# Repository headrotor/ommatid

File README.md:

# ommatid

Code and design files for my Ommatid spherical display/sensor array. 

* Here's an [Instructable about the enclosure and dome fabrication](http://www.instructables.com/id/Ommatid-Spherical-Display-constructing-the-enclosu/)
* Here's an [Instructable about the electronics and software](http://www.instructables.com/id/Ommatid-Spherical-Display-Electronics-Programming-/)

Here are the construction and code files:

* `cad` -- 3D cad files. Likely not so useful unless you have access to a Stratasys Objet 
* `PCB` -- Schematic and printed circuit board design files
* `firmware` -- C code for ATTiny firmware for PCBs
* `code` -- host code (Python) for Ommatid.
* `sim` -- simulator, in [processing.org](http://processing.org) Python environment

NB: code is still very much a work in progress!

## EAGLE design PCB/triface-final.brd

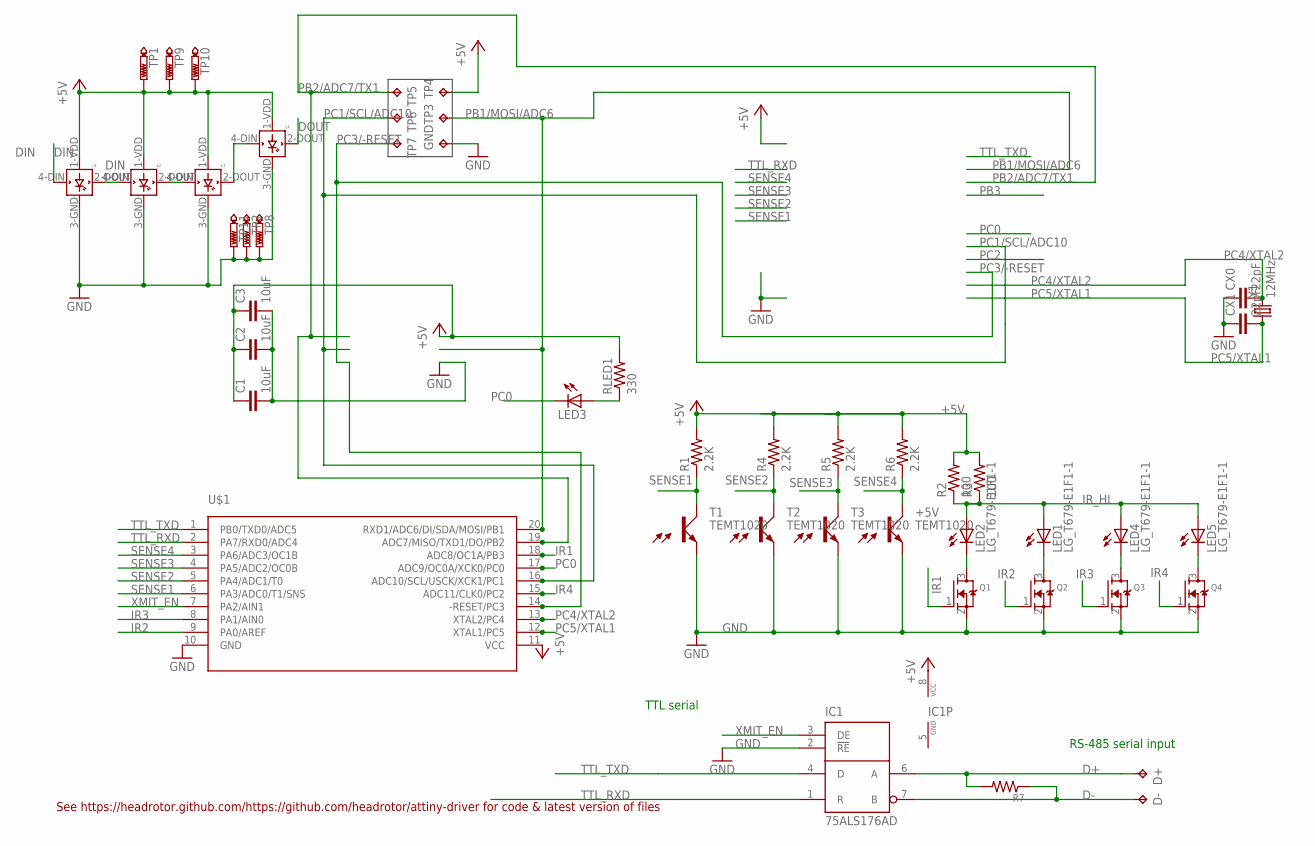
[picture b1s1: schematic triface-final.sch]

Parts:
+5V: TEMT1020
C1, C2, C3: 10uF; C0805
CX0, CX1: 22pF; C0603
D+: TPTP14R; TP14R
D-: TPTP14SQ; TP14SQ
GND: TPTP12SQ; TP12SQ
IC1: 75ALS176AD; SO-08
L1, L2, L3, L4: WS2812B
LED1, LED2, LED4, LED5: LG_T679-E1F1-1; PLCC2
LED3: LED0603; LED-0603
Q1, Q2, Q3, Q4: MOSFET-NREFLOW; SOT23
R1, R4, R5, R6: 2.2K; R0603
R2, R3: 100; R0805
R7: 330; R0603
RLED1: 330; 0603-RES
T1, T2, T3: TEMT1020
TP1, TP9, TP10: PTR1TP14SQ; TP14SQ
TP2, TP8, TP11: PTR1B2,54; B2,54
TP3, TP4, TP5, TP6, TP7: TPTP12R; TP12R
U$1: ATTINY1634; SOIC20
Y1: 12MHz; CRYSTAL-SMD-5X3

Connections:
+5V: C1.1, C2.1, C3.1, IC1.8 (VCC), L1.1-VDD (VDD), L2.1-VDD (VDD), L3.1-VDD (VDD), L4.1-VDD (VDD), R1.2, R2.2, R3.2, R4.2, R5.2, R6.2, RLED1.2, TP1.TP, TP4.TP, TP9.TP, TP10.TP, U$1.11 (VCC)
D+: D+.TP, IC1.6 (A), R7.2
D-: D-.TP, IC1.7 (B), R7.1
DIN: L1.4-DIN (DIN)
DOUT: L4.2-DOUT (DOUT)
GND: +5V.E, C1.2, C2.2, C3.2, CX0.1, CX1.1, GND.TP, IC1.2 (!RE), IC1.5 (GND), L1.3-GND (GND), L2.3-GND (GND), L3.3-GND (GND), L4.3-GND (GND), Q1.2 (S), Q2.2 (S), Q3.2 (S), Q4.2 (S), T1.E, T2.E, T3.E, TP2.TP, TP8.TP, TP11.TP, U$1.10 (GND)
IR1: Q1.1 (G), U$1.18 (ADC8/OC1A/PB3)
IR2: Q2.1 (G), U$1.9 (PA0/AREF)
IR3: Q3.1 (G), U$1.8 (PA1/AIN0)
IR4: Q4.1 (G), U$1.15 (ADC11/CLK0/PC2)
IR_HI: LED1.A, LED2.A, LED4.A, LED5.A, R2.1, R3.1
unnamed: LED2.C, Q1.3 (D)
unnamed: LED1.C, Q2.3 (D)
unnamed: L1.2-DOUT (DOUT), L2.4-DIN (DIN)
unnamed: LED3.A, RLED1.1
unnamed: L2.2-DOUT (DOUT), L3.4-DIN (DIN)
unnamed: L3.2-DOUT (DOUT), L4.4-DIN (DIN)
unnamed: LED4.C, Q3.3 (D)
unnamed: LED5.C, Q4.3 (D)
PB1/MOSI/ADC6: TP3.TP, U$1.20 (RXD1/ADC6/DI/SDA/MOSI/PB1)
PB2/ADC7/TX1: TP5.TP, U$1.19 (ADC7/MISO/TXD1/DO/PB2)
PC0: LED3.C, U$1.17 (ADC9/OC0A/XCK0/PC0)
PC1/SCL/ADC10: TP6.TP, U$1.16 (ADC10/SCL/USCK/XCK1/PC1)
PC3/-RESET: TP7.TP, U$1.14 (-RESET/PC3)
PC4/XTAL2: CX0.2, U$1.13 (XTAL2/PC4), Y1.3 (2)
PC5/XTAL1: CX1.2, U$1.12 (XTAL1/PC5), Y1.1
SENSE1: R1.1, T1.C, U$1.6 (PA3/ADC0/T1/SNS)
SENSE2: R4.1, T2.C, U$1.5 (PA4/ADC1/T0)
SENSE3: R5.1, T3.C, U$1.4 (PA5/ADC2/OC0B)
SENSE4: +5V.C, R6.1, U$1.3 (PA6/ADC3/OC1B)
TTL_RXD: IC1.1 (R), U$1.2 (PA7/RXD0/ADC4)
TTL_TXD: IC1.4 (D), U$1.1 (PB0/TXD0/ADC5)
XMIT_EN: IC1.3 (DE), U$1.7 (PA2/AIN1)

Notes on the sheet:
TTL serial
RS-485 serial input
See https://headrotor.github.com/https://github.com/headrotor/attiny-driver for code & latest version of files

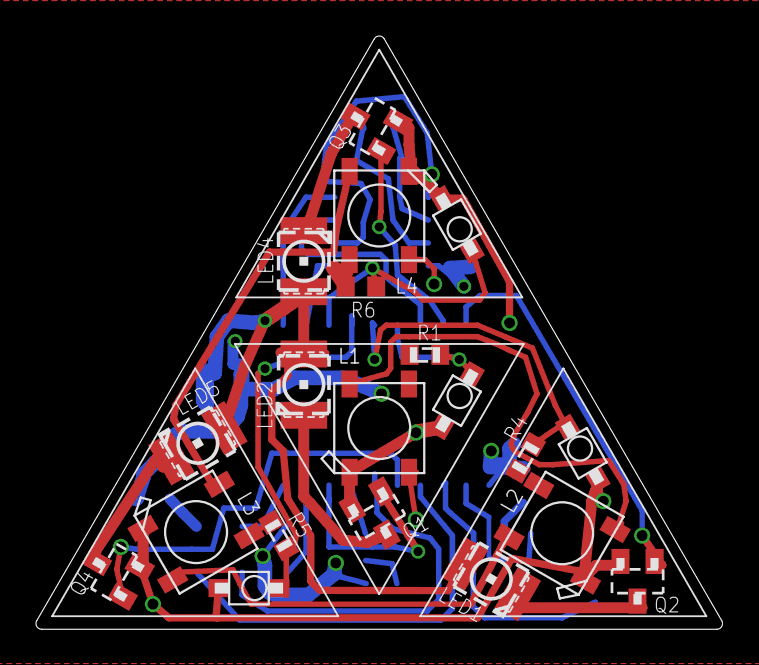
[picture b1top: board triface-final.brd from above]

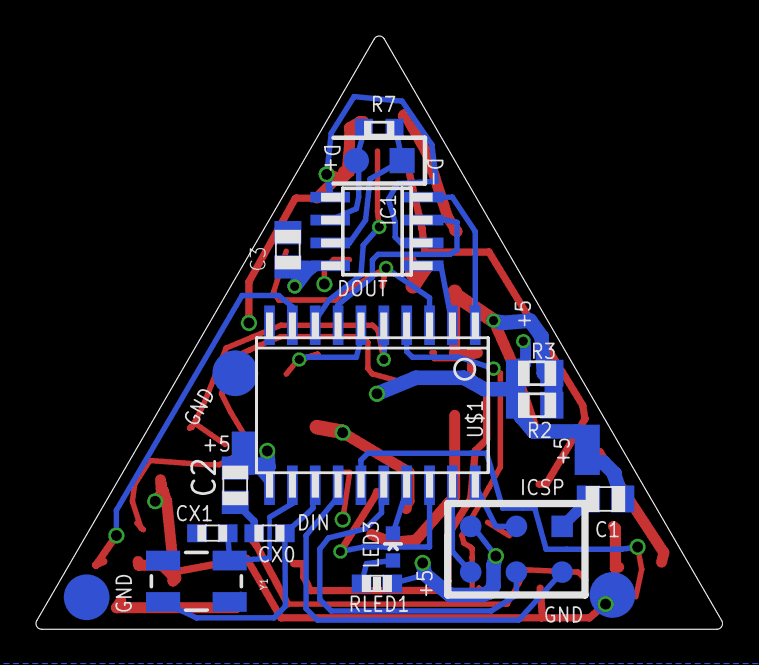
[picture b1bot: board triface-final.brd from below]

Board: 2 copper layers, 38.1 x 33.0 mm, 47 parts (27 on the bottom side), 31 nets.

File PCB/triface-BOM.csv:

"Part", "Value", "Device", "Package", "Description", "COLOR", "TP_SIGNAL_NAME", 
"+5V", "TEMT1020", "TEMT1020", "TEMT1020", "", "", "", 
"C1", "10uF", "C-EUC0805", "C0805", "CAPACITOR, European symbol", "", "", 
"C2", "10uF", "C-EUC0805", "C0805", "CAPACITOR, European symbol", "", "", 
"C3", "10uF", "C-EUC0805", "C0805", "CAPACITOR, European symbol", "", "", 
"CX0", "22pF", "C-EUC0603", "C0603", "CAPACITOR, European symbol", "", "", 
"CX1", "22pF", "C-EUC0603", "C0603", "CAPACITOR, European symbol", "", "", 
"IC1", "75ALS176AD", "75ALS176AD", "SO-08", "DIFFERENTIAL BUS TRANSCEIVERS", "", "", 
"L1", "WS2812B", "WS2812B", "WS2812B", "", "", "", 
"L2", "WS2812B", "WS2812B", "WS2812B", "", "", "", 
"L3", "WS2812B", "WS2812B", "WS2812B", "", "", "", 
"L4", "WS2812B", "WS2812B", "WS2812B", "", "", "", 
"LED1", "LG_T679-E1F1-1", "LG_T679-E1F1-1", "PLCC2", "LC TOPLED® Low Current LED", "green", "", 
"LED2", "LG_T679-E1F1-1", "LG_T679-E1F1-1", "PLCC2", "LC TOPLED® Low Current LED", "green", "", 
"LED3", "", "LED0603", "LED-0603", "LEDs", "", "", 
"LED4", "LG_T679-E1F1-1", "LG_T679-E1F1-1", "PLCC2", "LC TOPLED® Low Current LED", "green", "", 
"LED5", "LG_T679-E1F1-1", "LG_T679-E1F1-1", "PLCC2", "LC TOPLED® Low Current LED", "green", "", 
"Q1", "", "MOSFET-NREFLOW", "SOT23", "N-Channel Mosfet", "", "", 
"Q2", "", "MOSFET-NREFLOW", "SOT23", "N-Channel Mosfet", "", "", 
"Q3", "", "MOSFET-NREFLOW", "SOT23", "N-Channel Mosfet", "", "", 
"Q4", "", "MOSFET-NREFLOW", "SOT23", "N-Channel Mosfet", "", "", 
"R1", "2.2K", "R-US_R0603", "R0603", "RESISTOR, American symbol", "", "", 
"R2", "100", "R-US_R0805", "R0805", "RESISTOR, American symbol", "", "", 
"R3", "100", "R-US_R0805", "R0805", "RESISTOR, American symbol", "", "", 
"R4", "2.2K", "R-US_R0603", "R0603", "RESISTOR, American symbol", "", "", 
"R5", "2.2K", "R-US_R0603", "R0603", "RESISTOR, American symbol", "", "", 
"R6", "2.2K", "R-US_R0603", "R0603", "RESISTOR, American symbol", "", "", 
"R7", "330", "R-US_R0603", "R0603", "RESISTOR, American symbol", "", "", 
"RLED1", "330", "RESISTOR0603-RES", "0603-RES", "Resistor", "", "", 
"T1", "TEMT1020", "TEMT1020", "TEMT1020", "", "", "", 
"T2", "TEMT1020", "TEMT1020", "TEMT1020", "", "", "", 
"T3", "TEMT1020", "TEMT1020", "TEMT1020", "", "", "", 
"U$1", "ATTINY1634", "ATTINY1634", "SOIC20", "", "", "", 
"Y1", "12MHz", "CRYSTAL5X3", "CRYSTAL-SMD-5X3", "Various standard crystals. Proven footprints. Spark Fun Electronics SKU : COM-00534", "", "",

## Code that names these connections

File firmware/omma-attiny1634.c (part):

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// ATtiny1634 Pin map
//
//              +-\/-+
//   TXD  PB0  1|o   |20  PB1 MOSI
//   RXD  PA7  2|    |19  PB2 MISO
//        PA6  3|    |18  PB3
//        PA5  4|    |17  PC0
//        PA4  5|    |16  PC1 SCK
//        PA3  6|    |15  PC2
//XMIT_EN PA2  7|    |14  PC3 RESET
//        PA1  8|    |13  PC4
//        PA0  9|    |12  PC5
//        GND 10|    |11  VCC


// indicator LED on PC0
#define LED_C0 PC0

// Turn off all IR leds. To avoid overcurrent, ONLY ONE IR SHOULD BE ON AT A TIME

// IRLED 1: LED2 PB3 (center)
#define IRLED_B3 PB3
// IRLED 2: PA0
#define IRLED_A0 PA0
// IRLED 3: PC2
#define IRLED_C2 PC2
// IRLED 4: PA1
#define IRLED_A1 PA1


/// ADC stuff. ADCs are
// IR sensor 0: PA3-ADC0
// IR sensor 1: PA4-ADC1
// IR sensor 2: PA5-ADC2
// IR sensor 3: PA6-ADC3


// define buffers for averaging. 
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volatile uint8_t  adc_ptr = 0;


#define TXD0 PB0


#define MAX_COMMAND_LENGTH 24
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
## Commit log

2016-03-09 added some text
2016-03-09 add PCB files
2016-03-10 first add
2016-03-10 added text and links
2016-03-10 added text and image
2016-03-10 really add image file

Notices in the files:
parts and their libraries:
SparkFun-LED: Licensing: CC v3.0 Share-Alike You are welcome to use this library for commercial purposes.
